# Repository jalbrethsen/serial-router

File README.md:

# What it does
This project is to enable remote administration of machines through a USB serial port. You can have several machines connected to the serial router and as long as one of them is accessible over the network, you can use it to reach the other machines. This was motivated by the fact that I work remotely and also do a lot of SDN experiments that cause me to lose connectivity if something is misconfigured.

# How to build
I designed the PCB itself in KiCAD based around an Espressif Esp32-c6 chip with several CH340 USB-to-serial convertors. Everything is big enough to be hand solderable if needed, I used JLC PCB to build the PCB and assemble everything except the esp32 chip.

# Firmware Install
I use MicroPython for my firmware, it is easy to install, easy to use, and is well supported for Espressif devices. You can build from source or download the latest release from [Here](https://micropython.org/download/ESP32_GENERIC_C6/).

That download will give you a binary file that you can install to the chip using esptool.
```
pip install esptool
```
Then to push the firmware you would run the following:
```
esptool.py --port PORTNAME erase_flash
esptool.py --port PORTNAME --baud 460800 write_flash 0 FIRMWARE.bin
```
Where FIRMWARE.bin is the binary MicroPython firmware you downloaded or compiled and PORTNAME is the port when you plug the left most usb port into your computer. In my case it was /dev/ttyACM0, but it maybe /dev/ttyUSB0 or something else.

# Software Install
Now that you have the board running MicroPython, you can push the boot.py file to the board to run our serial router program. I use ampy to push files to esp chips, you can install it:
```
pip install adafruit-ampy
```
Now you can push the program which will run on boot in MicroPython
```
ampy --port /dev/ttyACM0 put boot.py /boot.py
```
Now the serial router should be running UART on the four right most usb ports and able to link between them.

# Create login shell
Now on all your machines that you want to remotely access (assuming they are running Linux):
```
sudo systemctl enable serial-getty@ttyUSB0.service
```
Replace ttyUSB0 with whatever the USB serial port shows up as.

# Access a machine
If this is running on 4 machines, you can use any 1 to access the other 3. Simple disable the login shell that is bound to the serial port:
```
sudo systemctl stop serial-getty@ttyUSB0.service
```
Next use a tool like tmux or screen to connect to the serial port
```
sudo screen /dev/ttyUSB0 9600
```
You may or may not need to specify the baud rate, I am using the default 9600 but you can also change this by modifying the boot.py and modifying the serial-getty@ttyUSB0.service.
Now that you have a screen session you can hold down the 0,1,2,3 key to connect to the login shell running bound to that specific USB port. When you are finished press ctl+d to tell the router to disconnect the ports, then close your screen session and start up your login shell again.
```
sudo systemctl start serial-getty@ttyUSB0.service
```
That's all there is to it.

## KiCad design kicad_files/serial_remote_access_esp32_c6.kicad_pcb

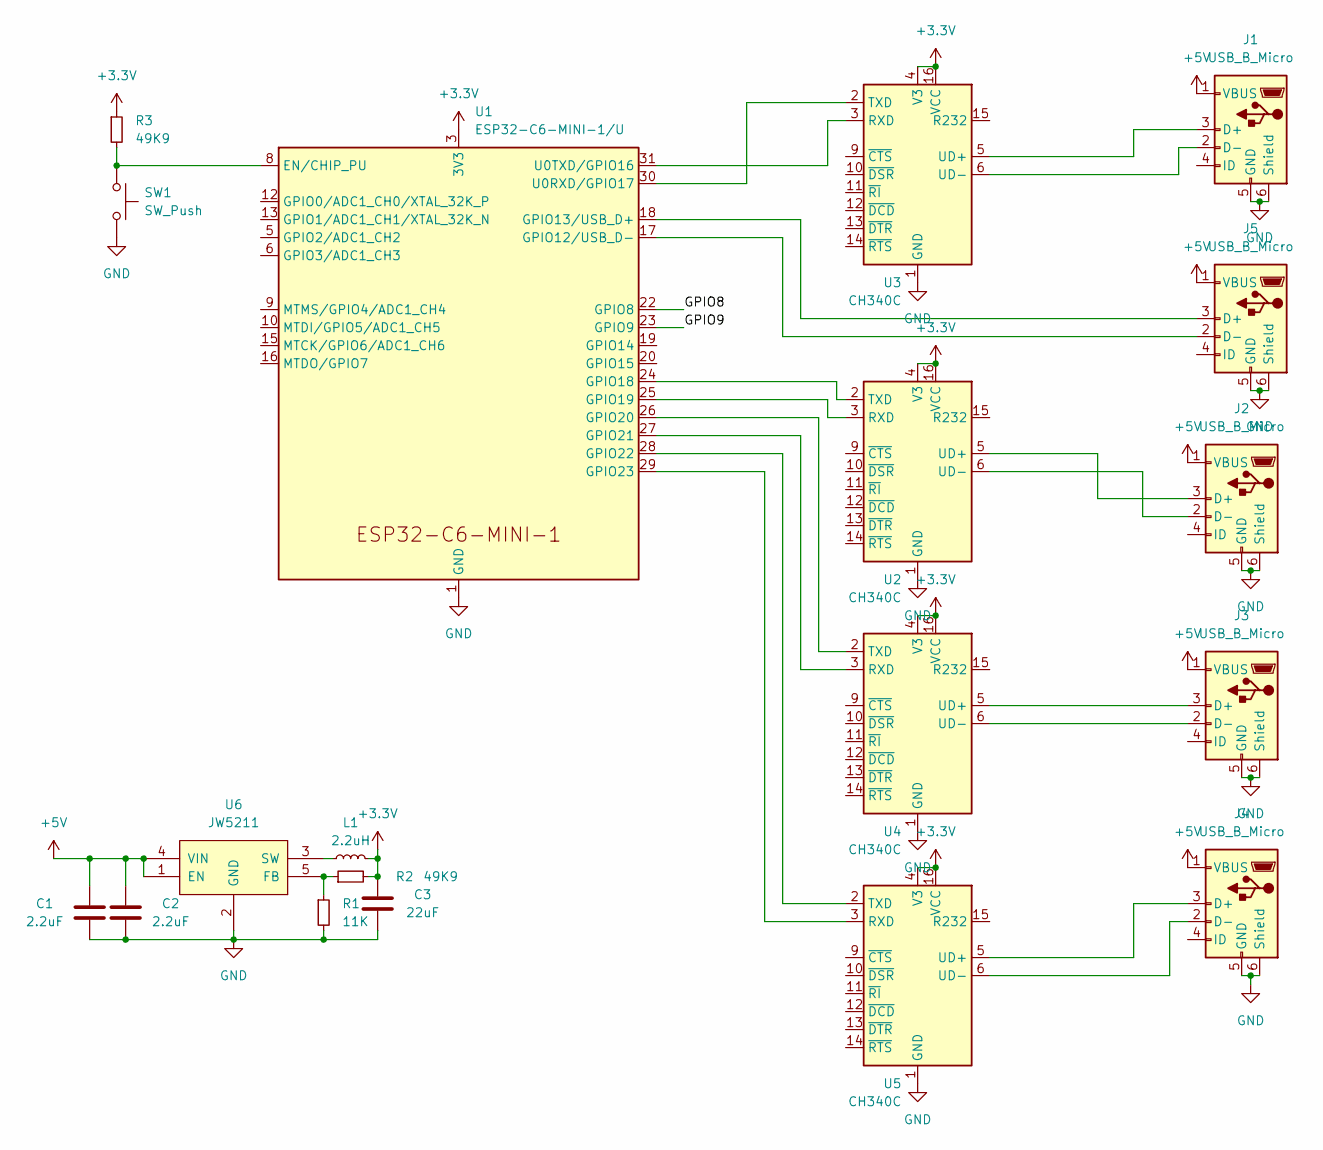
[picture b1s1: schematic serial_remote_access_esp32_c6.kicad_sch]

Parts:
C1, C2: 2.2uF; C_0402_1005Metric
C3: 22uF; C_0603_1608Metric
J1, J2, J3, J4, J5: USB_B_Micro; USB_Micro-B_Amphenol_10118194_Horizontal
L1: 2.2uH; L_0805_2012Metric
R1: 11K; R_0603_1608Metric
R2, R3: 49K9; R_0402_1005Metric
SW1: SW_Push; SW_SPST_CK_RS282G05A3
U1: ESP32-C6-MINI-1/U; ESP32-C6-MINI-1
U2, U3, U4, U5: CH340C; SOIC-16_3.9x9.9mm_P1.27mm
U6: JW5211; SOT-23-5

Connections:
+3.3V: C3.2, L1.2, R2.2, R3.1, U1.3 (3V3), U2.4 (V3), U2.16 (VCC), U3.4 (V3), U3.16 (VCC), U4.4 (V3), U4.16 (VCC), U5.4 (V3), U5.16 (VCC)
+5V: C1.2, C2.2, J1.1 (VBUS), J2.1 (VBUS), J3.1 (VBUS), J4.1 (VBUS), J5.1 (VBUS), U6.1 (EN), U6.4 (VIN)
/GPIO8: U1.22 (GPIO8)
/GPIO9: U1.23 (GPIO9)
GND: C1.1, C2.1, C3.1, J1.5 (GND), J1.6 (Shield), J2.5 (GND), J2.6 (Shield), J3.5 (GND), J3.6 (Shield), J4.5 (GND), J4.6 (Shield), J5.5 (GND), J5.6 (Shield), R1.2, SW1.2, U1.1 (GND), U1.2 (GND), U1.11 (GND), U1.14 (GND), U1.36 (GND), U1.37 (GND), U1.38 (GND), U1.39 (GND), U1.40 (GND), U1.41 (GND), U1.42 (GND), U1.43 (GND), U1.44 (GND), U1.45 (GND), U1.46 (GND), U1.47 (GND), U1.48 (GND), U1.49 (GND), U1.50 (GND), U1.51 (GND), U1.52 (GND), U1.53 (GND), U2.1 (GND), U3.1 (GND), U4.1 (GND), U5.1 (GND), U6.2 (GND)
unnamed: J1.3 (D+), U3.5 (UD+)
unnamed: J1.2 (D-), U3.6 (UD-)
unnamed: J2.3 (D+), U2.5 (UD+)
unnamed: J2.2 (D-), U2.6 (UD-)
unnamed: J3.3 (D+), U4.5 (UD+)
unnamed: J3.2 (D-), U4.6 (UD-)
unnamed: J4.3 (D+), U5.5 (UD+)
unnamed: J4.2 (D-), U5.6 (UD-)
unnamed: J5.3 (D+), U1.18 (GPIO13/USB_D+)
unnamed: J5.2 (D-), U1.17 (GPIO12/USB_D-)
unnamed: R3.2, SW1.1, U1.8 (EN/CHIP_PU)
unnamed: U1.24 (GPIO18), U2.2 (TXD)
unnamed: U1.25 (GPIO19), U2.3 (RXD)
unnamed: U1.26 (GPIO20), U4.2 (TXD)
unnamed: U1.27 (GPIO21), U4.3 (RXD)
unnamed: U1.28 (GPIO22), U5.2 (TXD)
unnamed: U1.29 (GPIO23), U5.3 (RXD)
unnamed: U1.30 (U0RXD/GPIO17), U3.2 (TXD)
unnamed: U1.31 (U0TXD/GPIO16), U3.3 (RXD)
unnamed: R1.1, R2.1, U6.5 (FB)
unnamed: L1.1, U6.3 (SW)

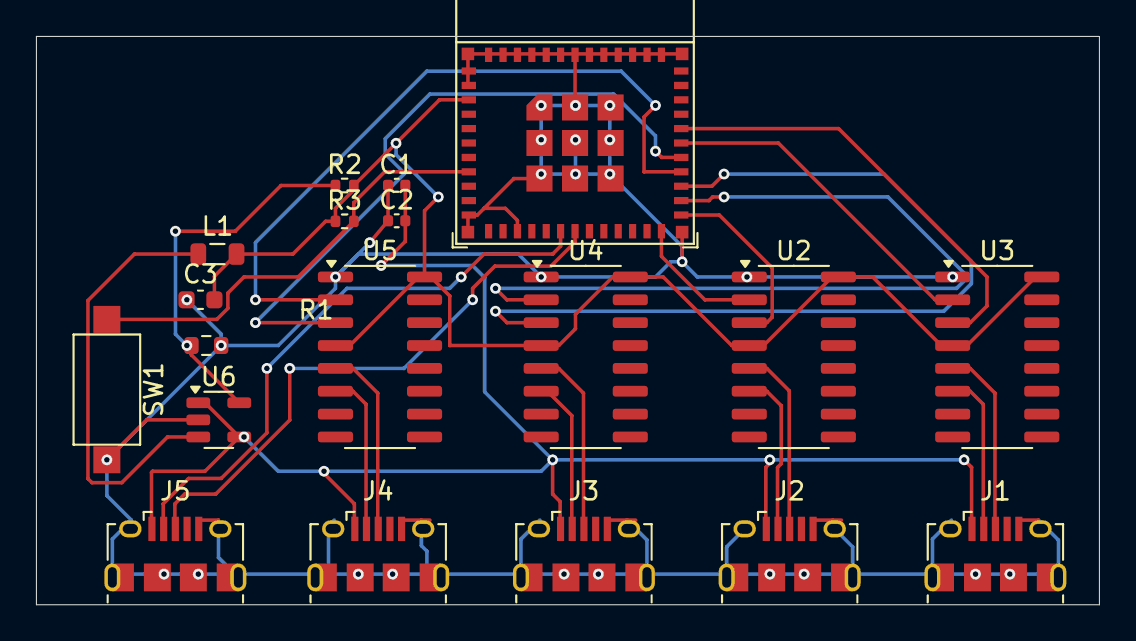
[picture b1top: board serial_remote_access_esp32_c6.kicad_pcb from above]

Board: 2 copper layers, 59.1 x 31.6 mm, 19 parts (0 on the bottom side), 24 nets.

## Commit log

2025-05-14 added kicad files for the pcb design
2025-05-14 Added README and boot.py
